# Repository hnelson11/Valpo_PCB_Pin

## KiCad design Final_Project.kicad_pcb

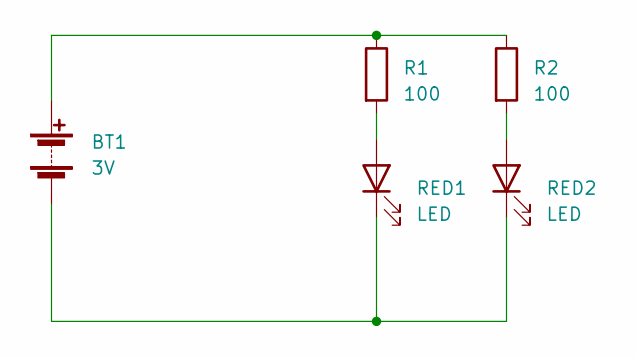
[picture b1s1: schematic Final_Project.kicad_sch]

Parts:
BT1: 3V; BatteryHolder_Keystone_3034_1x20mm
R1, R2: 100; R_Axial_DIN0309_L9.0mm_D3.2mm_P12.70mm_Horizontal
RED1, RED2: LED; LED_D3.0mm

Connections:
unnamed: BT1.1 (+), R1.1, R2.1
unnamed: BT1.2 (-), RED1.1 (K), RED2.1 (K)
unnamed: R1.2, RED1.2 (A)
unnamed: R2.2, RED2.2 (A)

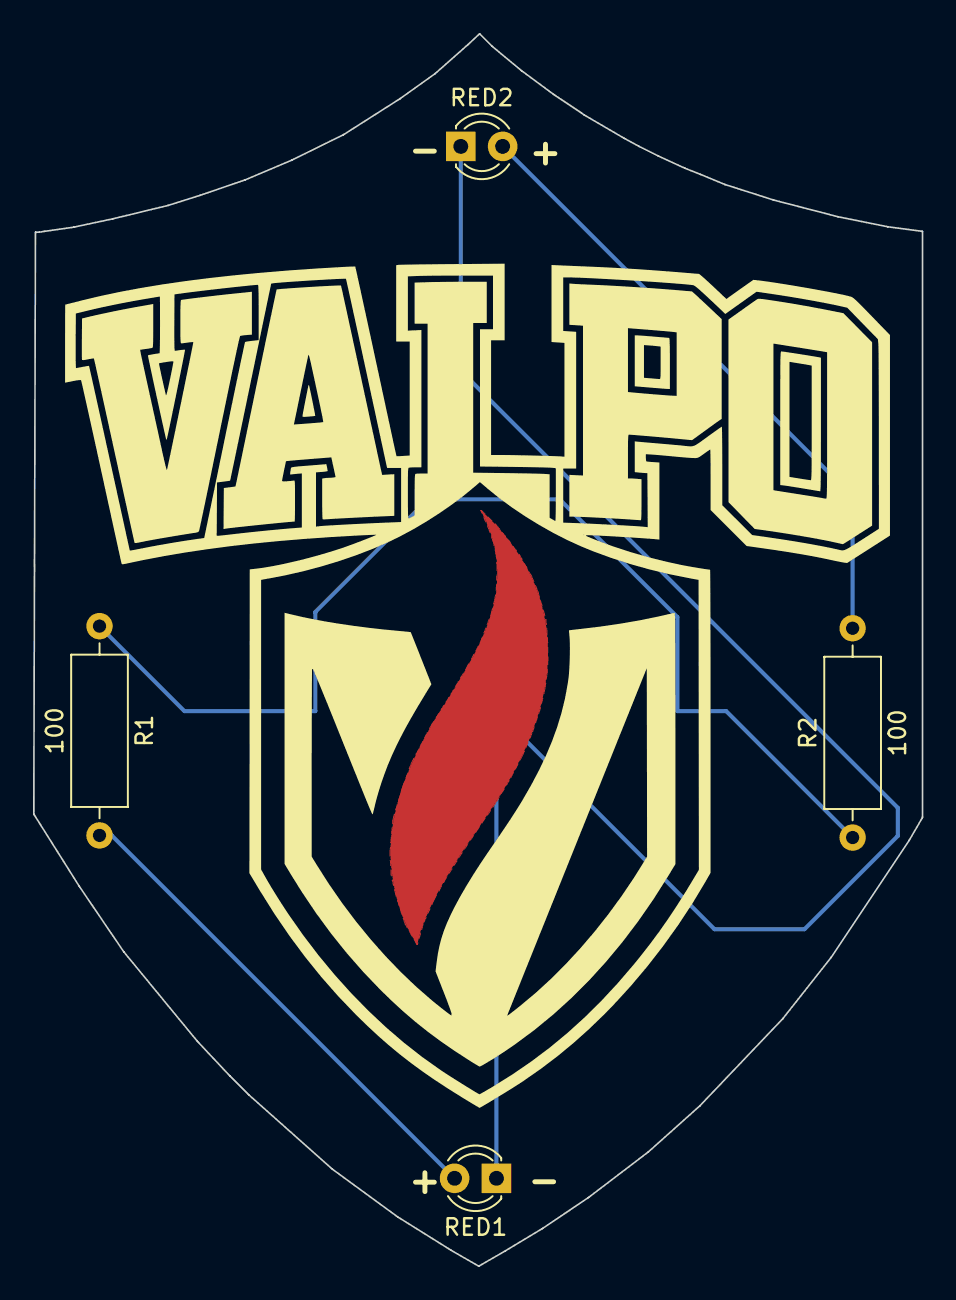
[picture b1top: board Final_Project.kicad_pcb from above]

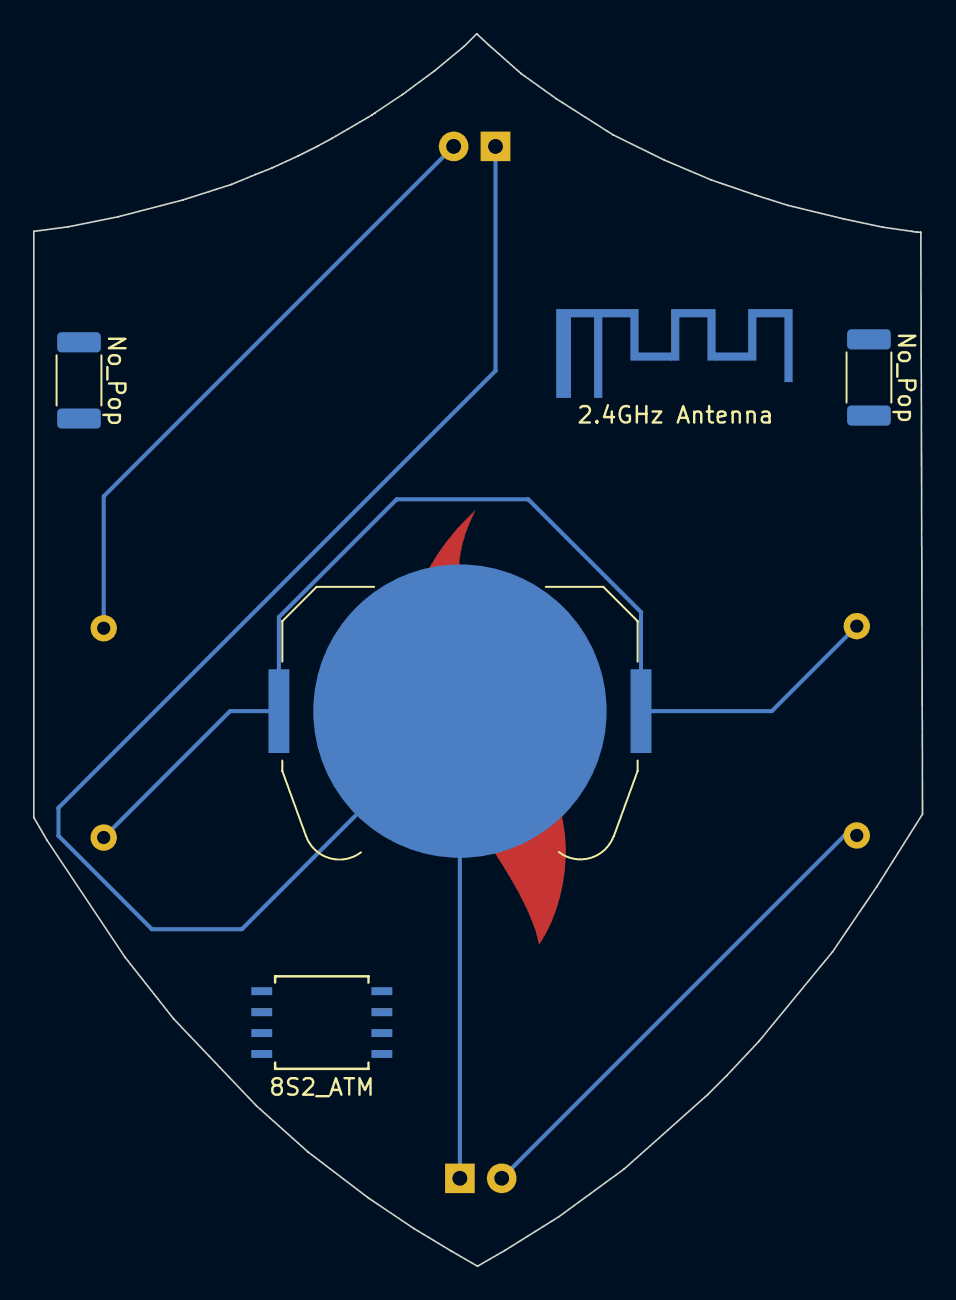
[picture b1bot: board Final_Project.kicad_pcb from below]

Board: 2 copper layers, 53.9 x 74.8 mm, 7 parts (3 on the bottom side), 4 nets.

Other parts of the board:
No_Pop: R_2010_5025Metric
No_Pop#2: R_2010_5025Metric

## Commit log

2023-05-05 V2 Files
